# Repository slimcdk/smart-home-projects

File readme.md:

# Smart Home Projects
This collection of projects aim to minimize costs and vendor lock in associated with building a smart based home. Some projects are alternatives to existing products, often with added redundancy or improved features, such as local or manual control. This ensures control over devices when either electricity, network or third parties fail and renders your home more useless than traditional homes.

### What is supported?
Everything evolves around Home Assistant with the powerful ESPHome firmware powering each device. Both Home Assistant and ESPHome aims for a high quality codebase and guarantees high reliability and stability.
However, as all projects are based on Espressifs ESP chips, any compatible firmware, such as Tasmota or even custom Arduino code, can be used. This also opens the possibility to use the devices with other smart home projects or standalone.

### Base configurations
To maximize efficiency is every ESPHome configuration importing a set of common sensors and utilities through the [*packages*](https://esphome.io/guides/configuration-types.html#packages) integration. Base configurations can be found [here](https://github.com/slimcdk/home-server/blob/master/services/esphome/common).

---
## Projects

## [Thermostatic Radiator Valve](./trv)
Status: *Migrating model to FreeCAD*

Build costs is about €18.

## [Tablet Wall Mount](./tablet-wall-mount)
Status: *Cleaning up project repository*

## [Aurora Portable Light Pole](./aurora)
Status: *Cleaning up project repository*

## [Halo Clock Light](./halo-clock)
Status: *Cleaning up project repository*

## [Motorized Roller Shades](./roller-shades)
Status: *Working on hardware for position feedback*

## [LK Fuga Compatible Insert](./lkf-series)
Status: *Working on designing base*

## [Smart mirror (MagicMirror) ](./smart-mirror)
Status: *Working on model in FreeCAD*

## [Envriomental Sensor](./environmental-sensor)
Status: *Migrating model to FreeCAD*

## [Build on Ceiling Lights](./ceiling-spot)
Status: *On the drawing board*

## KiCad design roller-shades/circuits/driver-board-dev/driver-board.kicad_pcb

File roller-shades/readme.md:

# Motorized Roller Shades

---
### Parts list
#### Assembly parts list

#### Setup parts lists

---
### Assembly guide

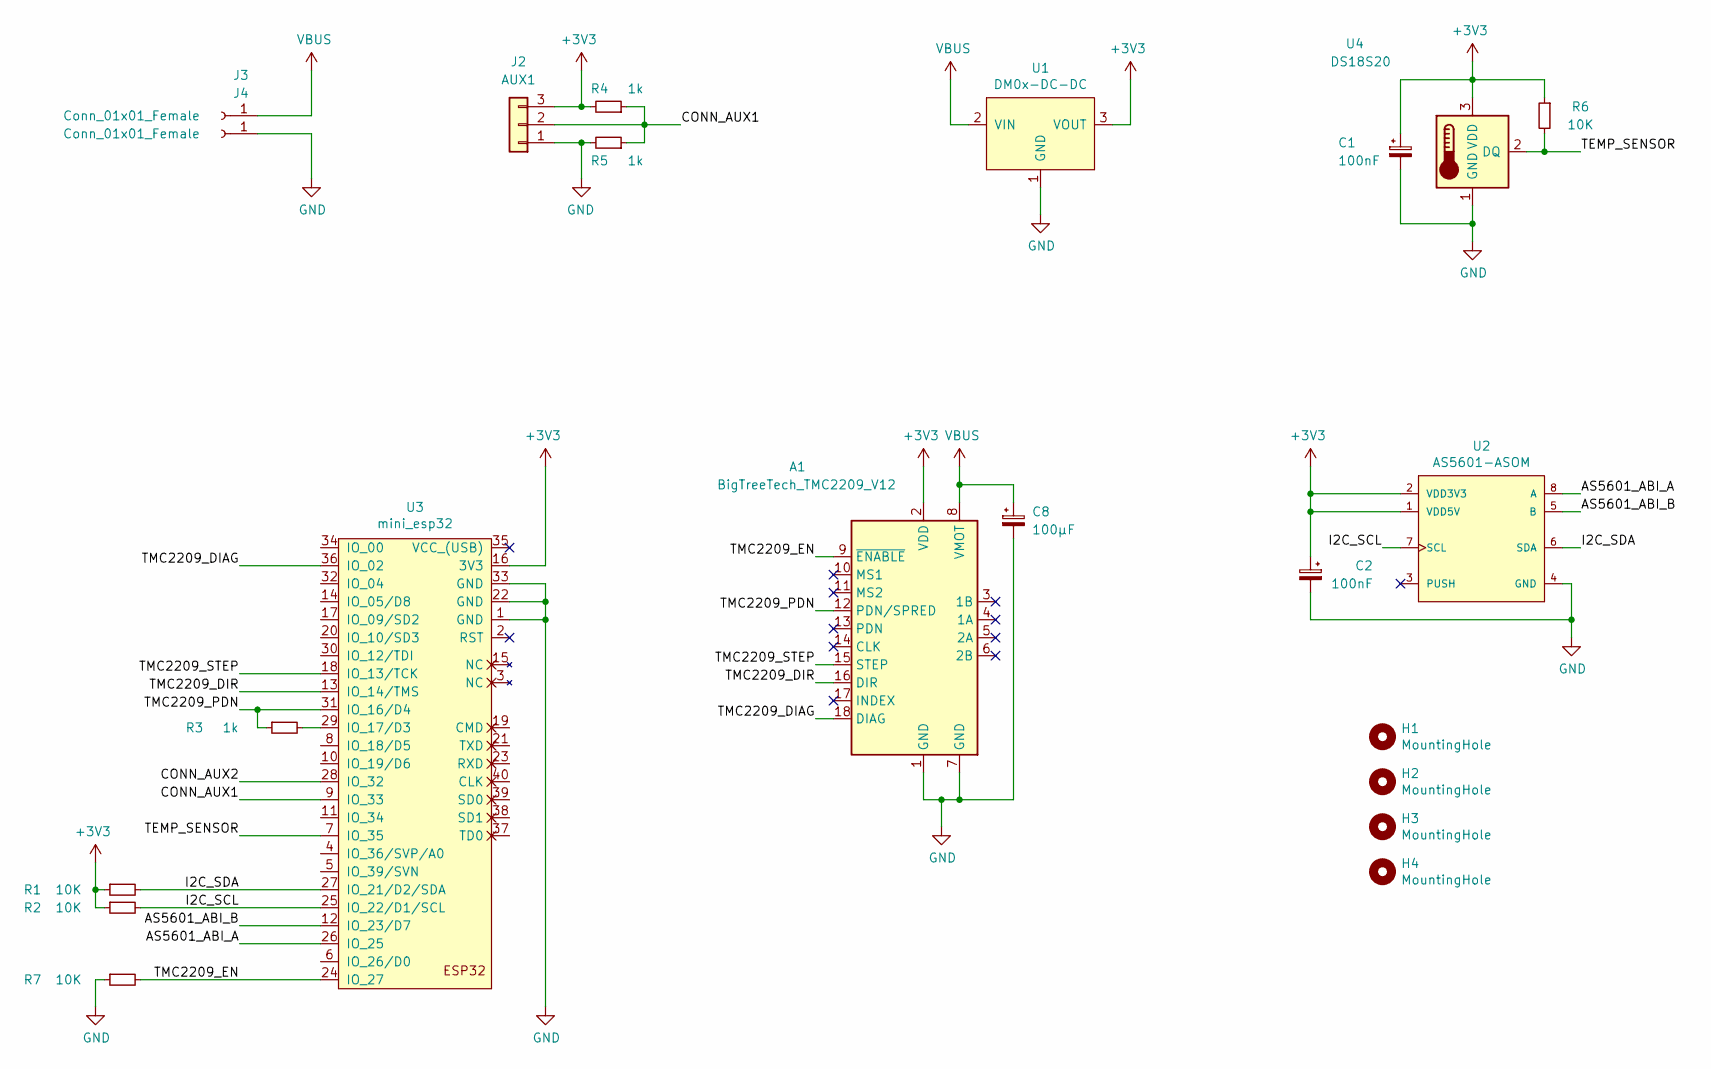
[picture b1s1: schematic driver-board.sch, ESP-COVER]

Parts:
A1: BigTreeTech_TMC2209_V12; BigTreeTech_TMC22xx_Breakout-16_15.2x20.3mm
C1, C2: 100nF; C_0805_2012Metric
C8: 100µF; CP_Radial_D5.0mm_P2.50mm
H1, H2, H3, H4: MountingHole; MountingHole_3.2mm_M3_DIN965_Pad
J2: AUX1; PinHeader_1x03_P2.54mm_Vertical
J3, J4: Conn_01x01_Female; TestPoint_THTPad_4.0x4.0mm_Drill2.0mm
R1, R2, R6, R7: 10K; R_0805_2012Metric_Pad1.20x1.40mm_HandSolder
R3, R4, R5: 1k; R_0805_2012Metric_Pad1.20x1.40mm_HandSolder
U1: DM0x-DC-DC; DM02-DC-DC
U2: AS5601-ASOM; Taos-AS5601-ASOM-0-0-0; mouser part number 985-AS5601-ASOM; digikey description ENCODER 12BIT PROGR A/B 8SOIC
U3: mini_esp32; Wemos_D1_mini32
U4: DS18S20; TO-92_Inline

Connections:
+3V3: A1.2 (VDD), C1.1, C2.1, J2.3, R1.1, R2.1, R4.2, R6.1, U1.3 (VOUT), U2.1 (VDD5V), U2.2 (VDD3V3), U3.16 (3V3), U4.3 (VDD)
/AS5601_ABI_A: U2.8 (A), U3.26 (IO_25)
/AS5601_ABI_B: U2.5 (B), U3.12 (IO_23/D7)
/CONN_AUX1: J2.2, R4.1, R5.1, U3.9 (IO_33)
/CONN_AUX2: U3.28 (IO_32)
/I2C_SCL: R2.2, U2.7 (SCL), U3.25 (IO_22/D1/SCL)
/I2C_SDA: R1.2, U2.6 (SDA), U3.27 (IO_21/D2/SDA)
/TEMP_SENSOR: R6.2, U3.7 (IO_35), U4.2 (DQ)
/TMC2209_DIAG: A1.18 (DIAG), U3.36 (IO_02)
/TMC2209_DIR: A1.16 (DIR), U3.13 (IO_14/TMS)
/TMC2209_EN: A1.9 (~ENABLE), R7.2, U3.24 (IO_27)
/TMC2209_PDN: A1.12 (PDN/SPRED), R3.1, U3.31 (IO_16/D4)
/TMC2209_STEP: A1.15 (STEP), U3.18 (IO_13/TCK)
GND: A1.1 (GND), A1.7 (GND), C1.2, C2.2, C8.2, J2.1, J4.1, R5.2, R7.1, U1.1 (GND), U2.4 (GND), U3.1 (GND), U3.22 (GND), U3.33 (GND), U4.1 (GND); also elsewhere on the board
unnamed: R3.2, U3.29 (IO_17/D3)
VBUS: A1.8 (VMOT), C8.1, J3.1, U1.2 (VIN); also elsewhere on the board

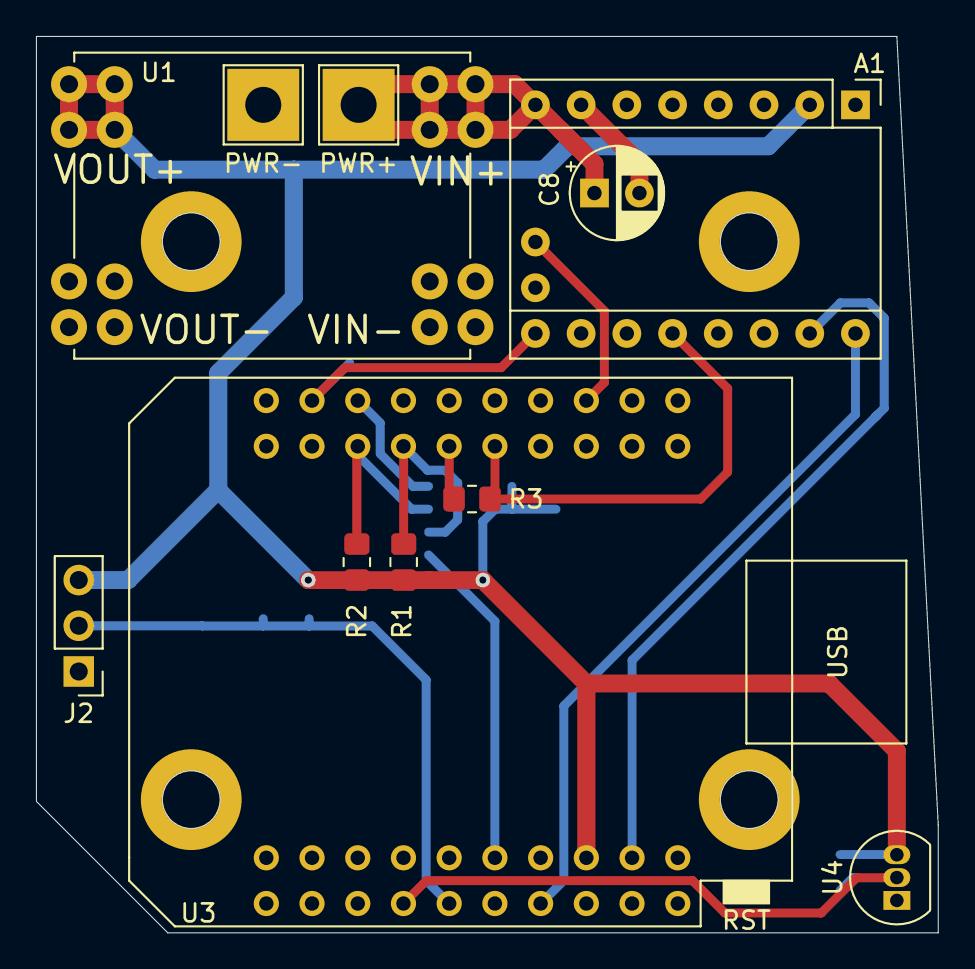
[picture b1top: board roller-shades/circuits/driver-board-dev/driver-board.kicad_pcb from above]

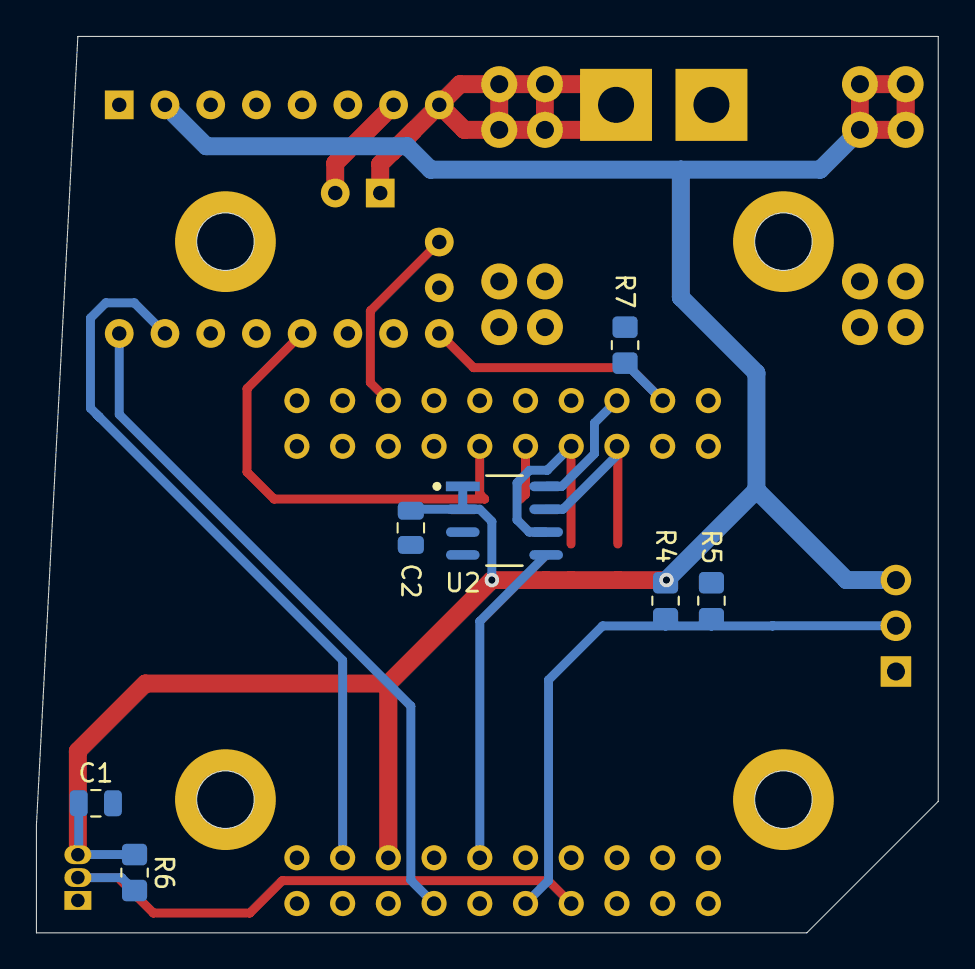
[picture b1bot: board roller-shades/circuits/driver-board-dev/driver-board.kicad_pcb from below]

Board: 2 copper layers, 50.1 x 49.8 mm, 22 parts (7 on the bottom side), 15 nets.

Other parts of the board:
PWR+: Conn_01x01_Female; TestPoint_THTPad_4.0x4.0mm_Drill2.0mm
PWR-: Conn_01x01_Female; TestPoint_THTPad_4.0x4.0mm_Drill2.0mm

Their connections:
GND: PWR-.1; also elsewhere on the board
VBUS: PWR+.1; also elsewhere on the board

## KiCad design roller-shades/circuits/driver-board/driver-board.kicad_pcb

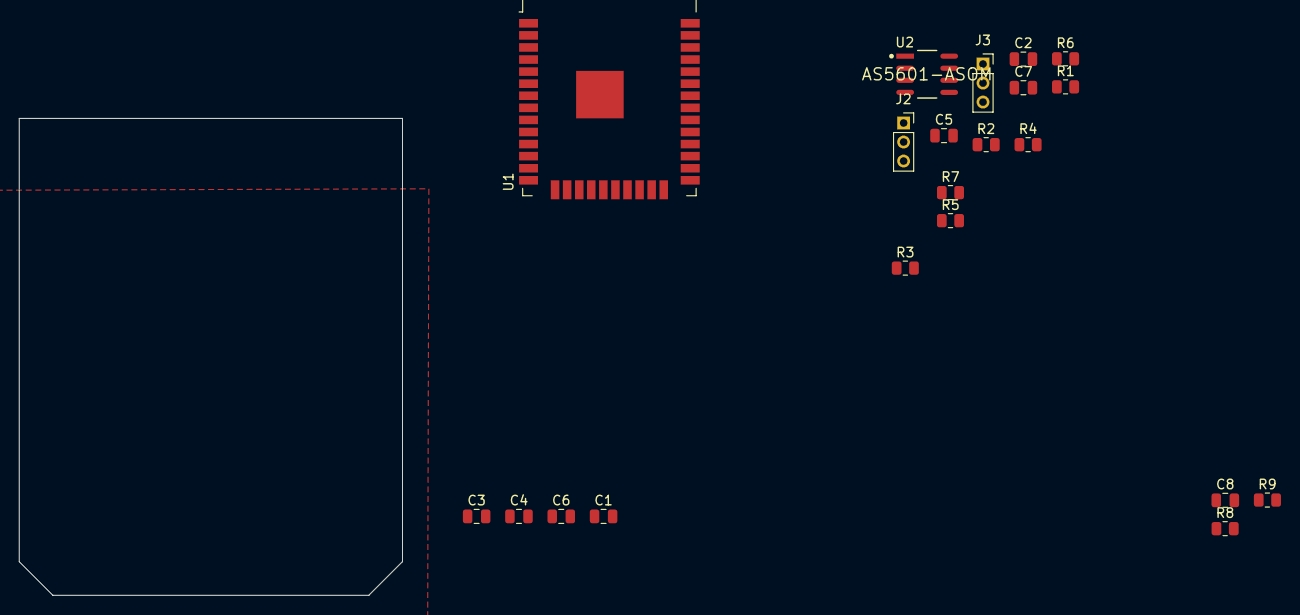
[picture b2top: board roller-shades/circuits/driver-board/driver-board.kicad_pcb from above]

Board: 2 copper layers, 40.3 x 50.1 mm, 21 parts (0 on the bottom side), 8 nets, no tracks yet.

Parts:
C1: 10µF 50V; C_0805_2012Metric
C2, C3, C7: 100nF; C_0805_2012Metric
C4: 220pF; C_0805_2012Metric
C5: NS; C_0805_2012Metric
C6: 22µF 6.3V; C_0805_2012Metric
C8: 100µF; C_0805_2012Metric
J2: AUX1; PinSocket_1x03_P2.00mm_Vertical
J3: AUX2; PinSocket_1x03_P2.00mm_Vertical
R1: 100K; R_0805_2012Metric
R2: 24.9K; R_0805_2012Metric
R3: 200K; R_0805_2012Metric
R4: 68.1K; R_0805_2012Metric
R5: 124K; R_0805_2012Metric
R6: 40.2K; R_0805_2012Metric
R7: 10K; R_0805_2012Metric
R8, R9: ??R; R_0805_2012Metric
U1: ESP32-WROOM-32
U2: AS5601-ASOM; Taos-AS5601-ASOM-0-0-0

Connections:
+3V3: C2.1, C6.1, C7.1, J2.3, J3.3, R5.2, R7.2, U2.1, U2.2
GND: C1.1, C2.2, C5.2, C6.2, C7.2, C8.2, J2.1, J3.1, R2.1, R3.2, R4.1, R6.1, R8.2, R9.2, U2.4
unnamed: C4.1, R4.2
unnamed: C4.2, C5.1
unnamed: R1.1, R2.2
unnamed: R5.1, R6.2
unnamed: U1.1, U1.15, U1.38, U1.39
VBUS: C1.2, C8.1, R1.2

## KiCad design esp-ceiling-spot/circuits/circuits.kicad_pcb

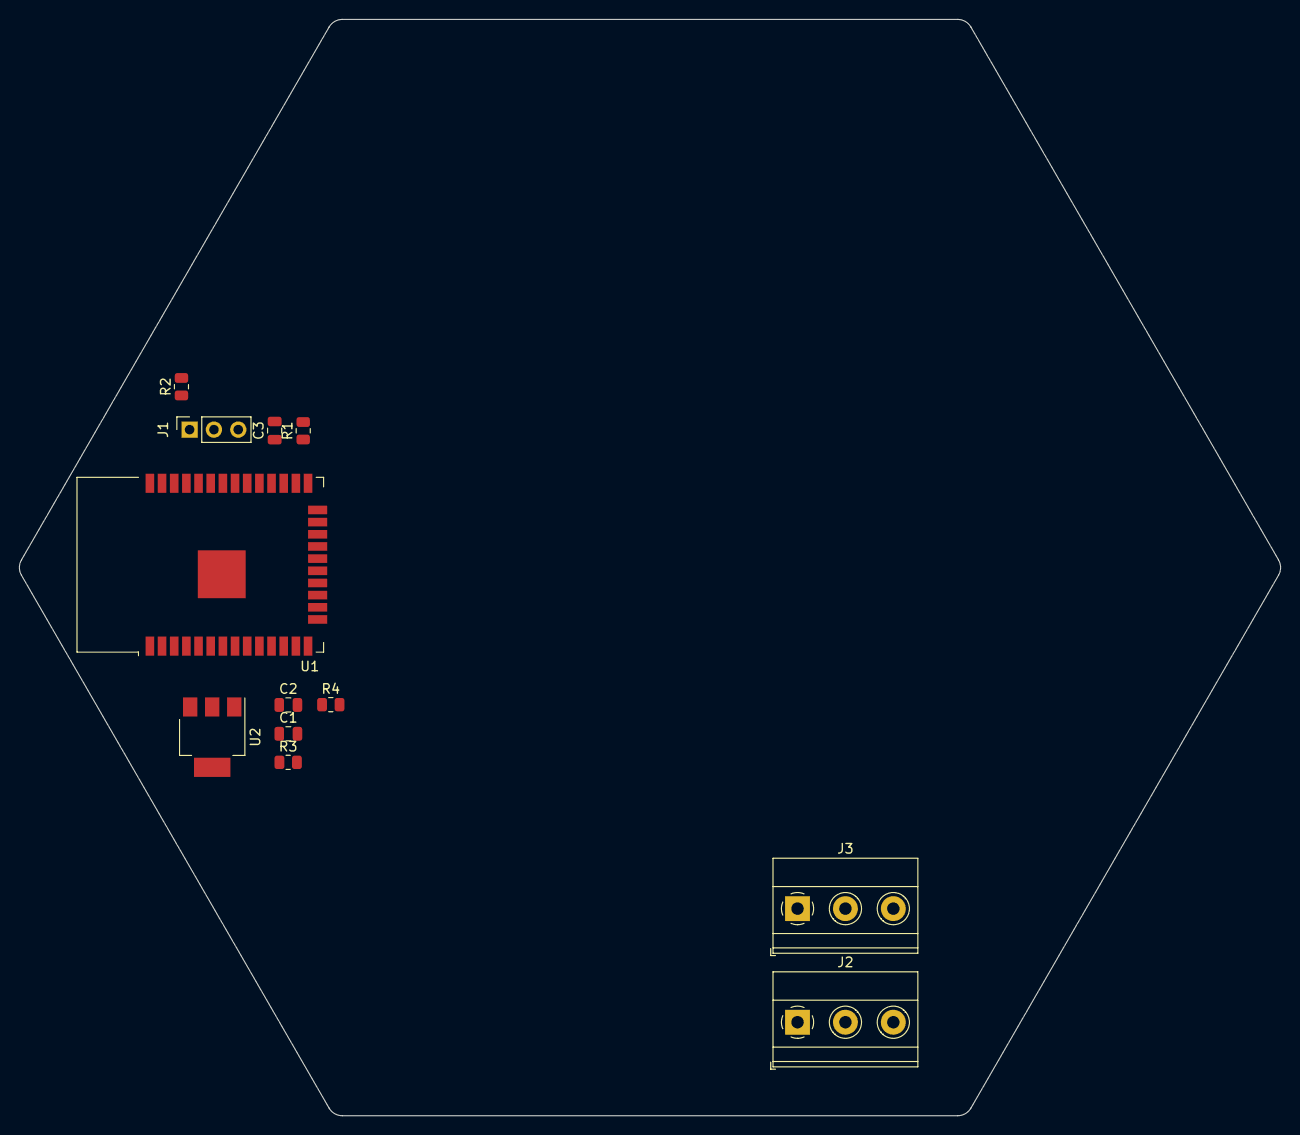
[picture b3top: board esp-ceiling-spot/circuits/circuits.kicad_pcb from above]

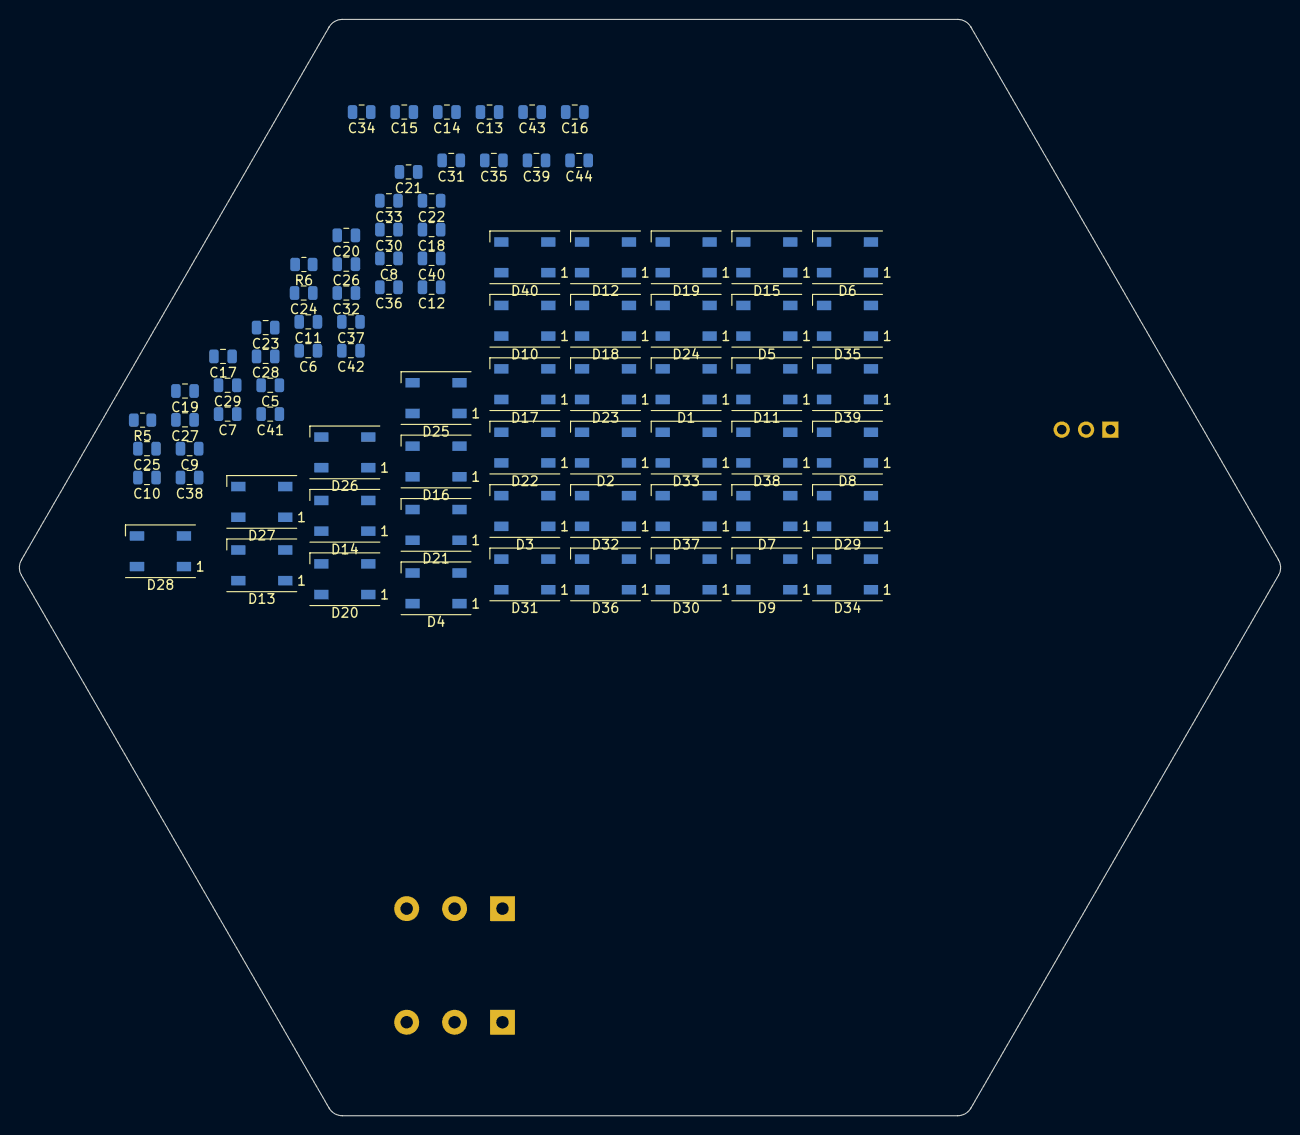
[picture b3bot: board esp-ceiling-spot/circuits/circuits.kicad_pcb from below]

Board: 2 copper layers, 131.7 x 114.4 mm, 94 parts (82 on the bottom side), 53 nets, no tracks yet.

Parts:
C1: 10µF; C_0805_2012Metric
C2: 22µF; C_0805_2012Metric
C3: ESP 10µF 0805; C_0805_2012Metric
C5, C6, C7, C8, C9, C10, C11, C12, C13, C14, C15, C16, C17, C18, C19, C20, C21, C22, C23, C24, C25, C26, C27, C28, C29, C30, C31, C32, C33, C34, C35, C36, C37, C38, C39, C40, C41, C42, C43, C44: 100nF; C_0805_2012Metric
D1, D2, D3, D4, D5, D6, D7, D8, D9, D10, D11, D12, D13, D14, D15, D16, D17, D18, D19, D20, D21, D22, D23, D24, D25, D26, D27, D28, D29, D30, D31, D32, D33, D34, D35, D36, D37, D38, D39, D40: WS2812B; LED_WS2812B_PLCC4_5.0x5.0mm_P3.2mm
J1: RGB LED RING; PinSocket_1x03_P2.54mm_Vertical
J2, J3: External 230AC; TerminalBlock_Phoenix_MKDS-1,5-3_1x03_P5.00mm_Horizontal
R1, R2, R3, R4: 10K 0805; R_0805_2012Metric
R5, R6: 500R; R_0805_2012Metric
U1: ESP32-WROOM-32D; ESP32-WROOM-32
U2: AMS1117-3.3; SOT-223-3_TabPin2

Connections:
+3V3: C2.1, C3.1, R1.1, R2.1, R3.1, U1.2, U2.2
+5V: C1.1, C5.1, C6.1, C7.1, C8.1, C9.1, C10.1, C11.1, C12.1, C13.1, C14.1, C15.1, C16.1, C17.1, C18.1, C19.1, C20.1, C21.1, C22.1, C23.1, C24.1, C25.1, C26.1, C27.1, C28.1, C29.1, C30.1, C31.1, C32.1, C33.1, C34.1, C35.1, C36.1, C37.1, C38.1, C39.1, C40.1, C41.1, C42.1, C43.1, C44.1, D1.1, D2.1, D3.1, D4.1, D5.1, D6.1, D7.1, D8.1, D9.1, D10.1, D11.1, D12.1, D13.1, D14.1, D15.1, D16.1, D17.1, D18.1, D19.1, D20.1, D21.1, D22.1, D23.1, D24.1, D25.1, D26.1, D27.1, D28.1, D29.1, D30.1, D31.1, D32.1, D33.1, D34.1, D35.1, D36.1, D37.1, D38.1, D39.1, D40.1, J1.1, U2.3
/EARTH: J2.3, J3.3
/ESP_EN: R1.2, U1.3
/ESP_IO5: R2.2, U1.29
/ESP_IO12: R4.2, U1.14
/ESP_IO15: R3.2, U1.23
/LIVE: J2.2, J3.2
/NEUTRAL: J2.1, J3.1
/RGB_RING_SIG: J1.2, U1.27
/RGB_SIG: R5.2, U1.28
GND: C1.2, C2.2, C3.2, C5.2, C6.2, C7.2, C8.2, C9.2, C10.2, C11.2, C12.2, C13.2, C14.2, C15.2, C16.2, C17.2, C18.2, C19.2, C20.2, C21.2, C22.2, C23.2, C24.2, C25.2, C26.2, C27.2, C28.2, C29.2, C30.2, C31.2, C32.2, C33.2, C34.2, C35.2, C36.2, C37.2, C38.2, C39.2, C40.2, C41.2, C42.2, C43.2, C44.2, D1.3, D2.3, D3.3, D4.3, D5.3, D6.3, D7.3, D8.3, D9.3, D10.3, D11.3, D12.3, D13.3, D14.3, D15.3, D16.3, D17.3, D18.3, D19.3, D20.3, D21.3, D22.3, D23.3, D24.3, D25.3, D26.3, D27.3, D28.3, D29.3, D30.3, D31.3, D32.3, D33.3, D34.3, D35.3, D36.3, D37.3, D38.3, D39.3, D40.3, J1.3, R4.1, R6.1, U1.1, U1.15, U1.38, U1.39, U2.1
unnamed: D1.2, D5.4
unnamed: D1.4, R5.1
unnamed: D2.2, D6.4
unnamed: D2.4, D37.2
unnamed: D3.2, D7.4
unnamed: D3.4, D38.2
unnamed: D4.2, D8.4
unnamed: D5.2, D9.4
unnamed: D10.2, D14.4
unnamed: D6.2, D10.4
unnamed: D11.2, D15.4
unnamed: D7.2, D11.4
unnamed: D12.2, D16.4
unnamed: D8.2, D12.4
unnamed: D13.2, D17.4
unnamed: D9.2, D13.4
unnamed: D14.2, D18.4
unnamed: D15.2, D19.4
unnamed: D16.2, D20.4
unnamed: D17.2, D21.4
unnamed: D18.2, D22.4
unnamed: D19.2, D23.4
unnamed: D20.2, D24.4
unnamed: D21.2, D25.4
unnamed: D22.2, D26.4
unnamed: D23.2, D27.4
unnamed: D24.2, D28.4
unnamed: D25.2, D29.4
unnamed: D26.2, D30.4
unnamed: D27.2, D31.4
unnamed: D28.2, D32.4
unnamed: D29.2, D33.4
unnamed: D30.2, D34.4
unnamed: D31.2, D35.4
unnamed: D32.2, D36.4
unnamed: D33.2, D37.4
unnamed: D34.2, D38.4
unnamed: D35.2, D39.4
unnamed: D36.2, D40.4
unnamed: D4.4, D39.2
unnamed: D40.2, R6.2

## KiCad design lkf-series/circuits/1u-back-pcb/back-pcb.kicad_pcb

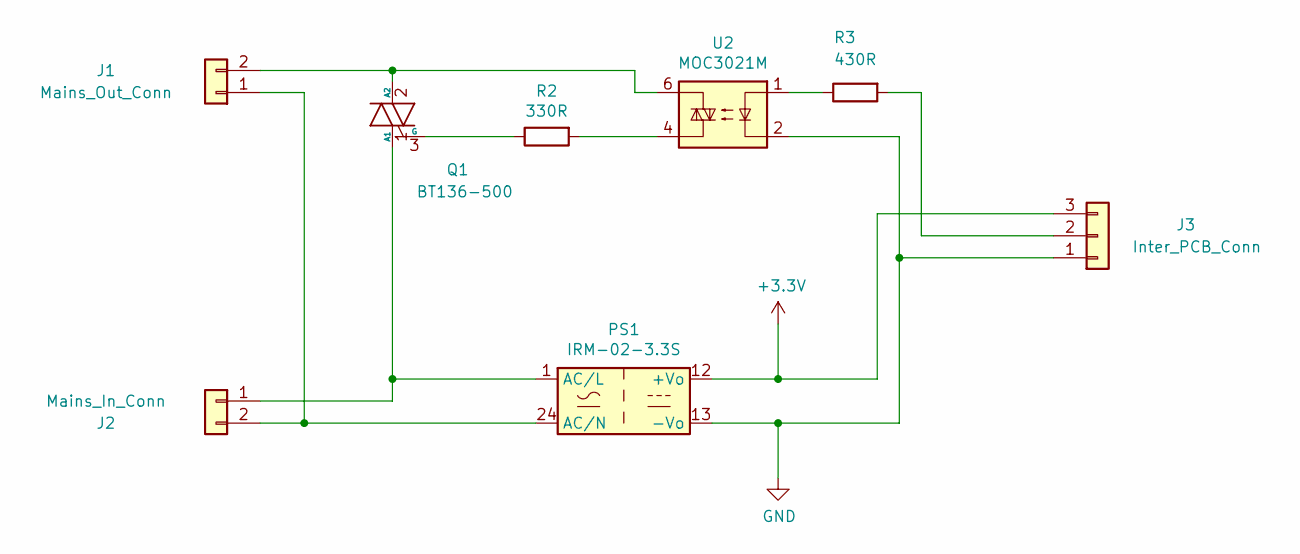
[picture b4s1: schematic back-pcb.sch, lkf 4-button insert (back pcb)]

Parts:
J1: Mains_Out_Conn; 2061-602_998-404
J2: Mains_In_Conn; 2061-602_998-404
J3: Inter_PCB_Conn; PinHeader_1x03_P2.54mm_Vertical
PS1: IRM-02-3.3S; Converter_ACDC_MeanWell_IRM-02-xx_SMD
Q1: BT136-500; TO-252-2
R2: 330R; R_1210_3225Metric
R3: 430R; R_0603_1608Metric
U2: MOC3021M; DIP-6_W7.62mm_SMDSocket_SmallPads

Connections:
+3V3: J3.3, PS1.12 (+Vo)
GND: J3.1, PS1.13 (-Vo), U2.2
unnamed: J1.1, J2.2, PS1.24 (AC/N)
unnamed: J1.2, Q1.2 (A2), U2.6
unnamed: J2.1, PS1.1 (AC/L), Q1.1 (A1)
unnamed: J3.2, R3.2
unnamed: Q1.3 (G), R2.1
unnamed: R2.2, U2.4
unnamed: R3.1, U2.1

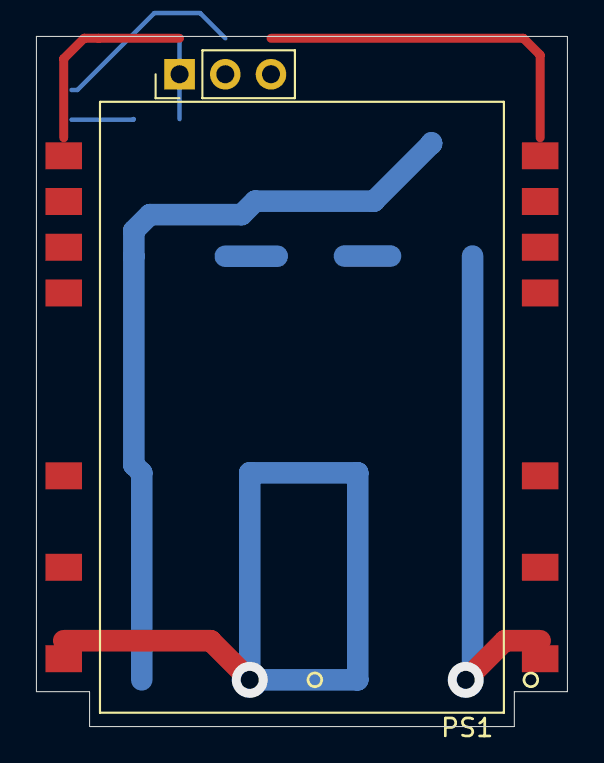
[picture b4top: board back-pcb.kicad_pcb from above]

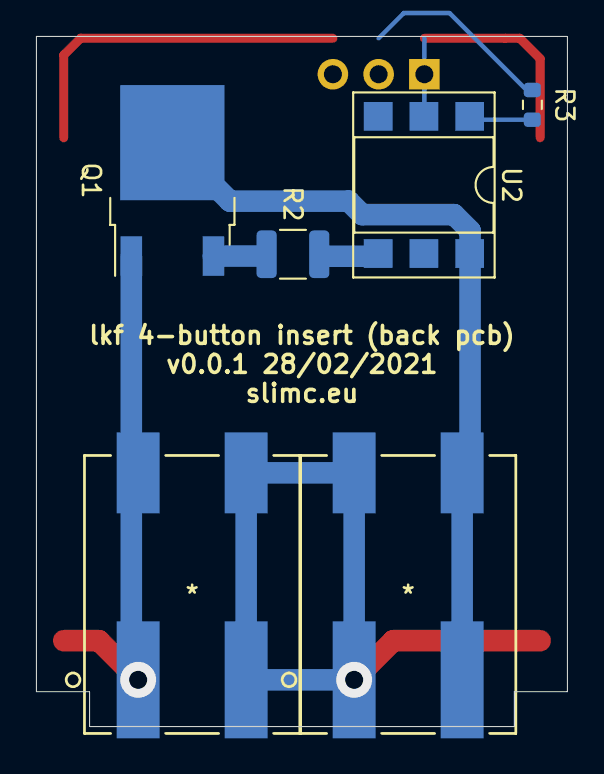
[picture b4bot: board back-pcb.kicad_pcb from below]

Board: 2 copper layers, 29.5 x 38.3 mm, 8 parts (6 on the bottom side), 9 nets.

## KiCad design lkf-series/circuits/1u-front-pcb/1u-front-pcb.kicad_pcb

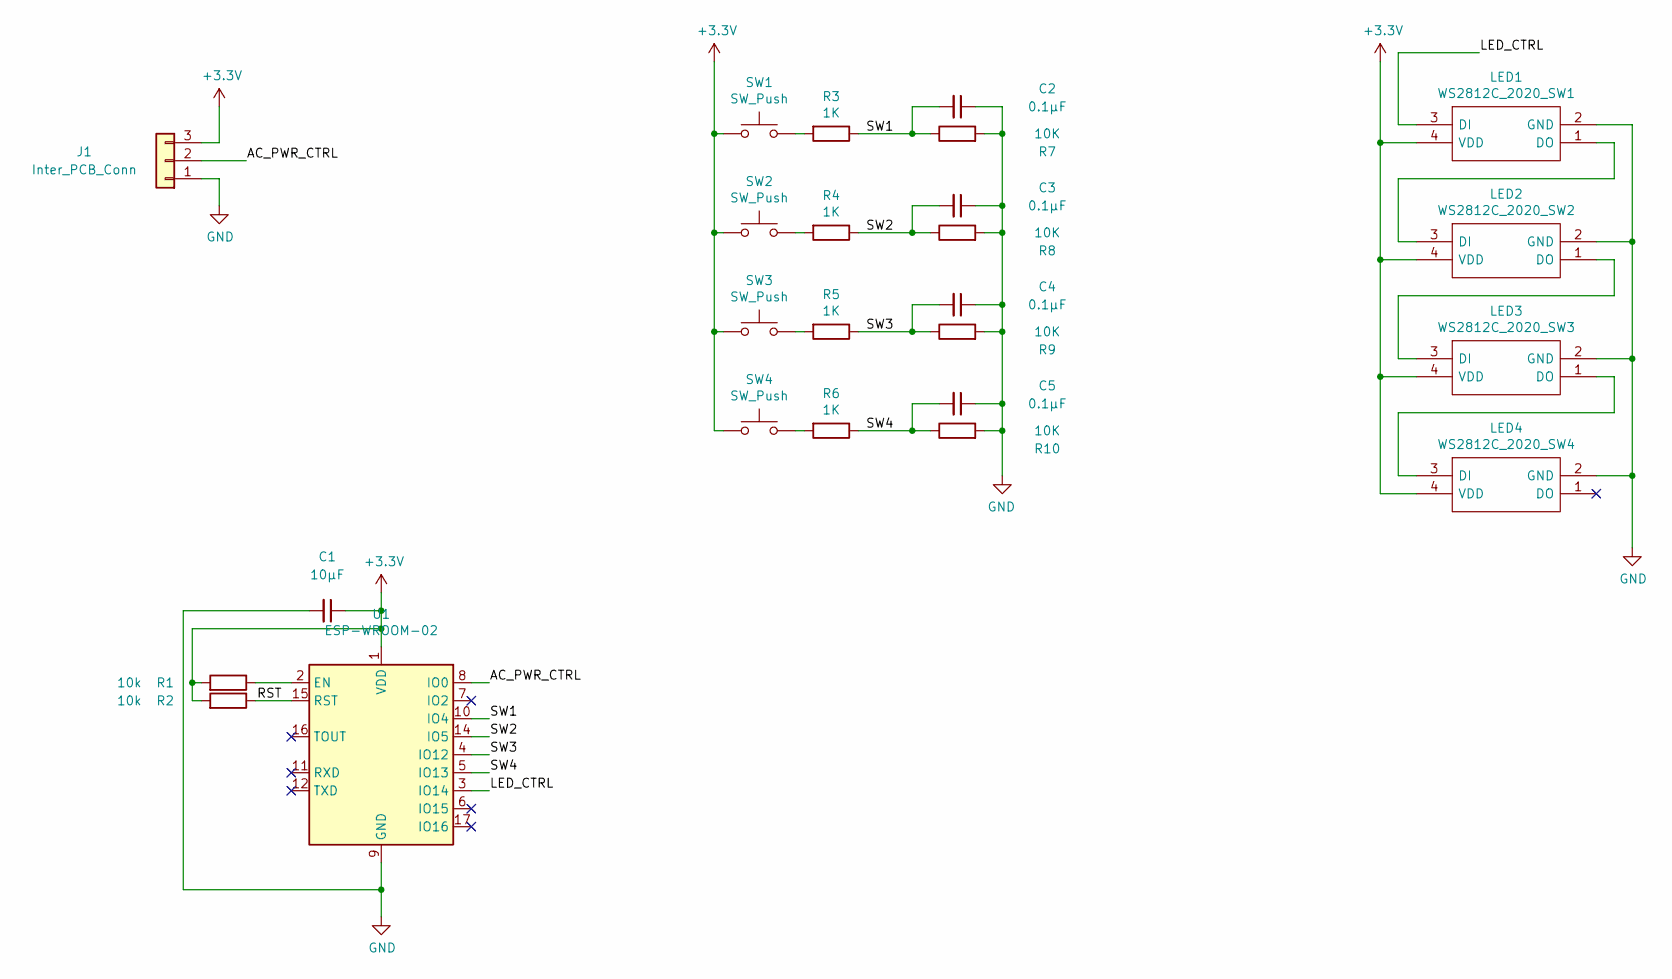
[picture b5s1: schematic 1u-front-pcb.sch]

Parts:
C1: 10µF; C_0603_1608Metric
C2, C3, C4, C5: 0.1µF; C_0603_1608Metric
J1: Inter_PCB_Conn; PinHeader_1x03_P2.54mm_Vertical
LED1: WS2812C_2020_SW1; WS2812C2020; Manufacturer_Part_Number WS2812C-2020
LED2: WS2812C_2020_SW2; WS2812C2020; Manufacturer_Part_Number WS2812C-2020
LED3: WS2812C_2020_SW3; WS2812C2020; Manufacturer_Part_Number WS2812C-2020
LED4: WS2812C_2020_SW4; WS2812C2020; Manufacturer_Part_Number WS2812C-2020
R1, R2: 10k; R_0603_1608Metric
R3, R4, R5, R6: 1K; R_0603_1608Metric
R7, R8, R9, R10: 10K; R_0603_1608Metric
SW1, SW2, SW3, SW4: SW_Push; SW_SPST_TL3342
U1: ESP-WROOM-02

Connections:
+3V3: C1.1, J1.3, LED1.4 (VDD), LED2.4 (VDD), LED3.4 (VDD), LED4.4 (VDD), R1.2, R2.2, SW1.1, SW2.1, SW3.1, SW4.1, U1.1 (VDD)
/AC_PWR_CTRL: J1.2, U1.8 (IO0)
/LED_CTRL: LED1.3 (DI), U1.3 (IO14)
/RST: R2.1, U1.15 (RST)
/SW1: C2.2, R3.1, R7.1, U1.10 (IO4)
/SW2: C3.2, R4.1, R8.1, U1.14 (IO5)
/SW3: C4.2, R5.1, R9.1, U1.4 (IO12)
/SW4: C5.2, R6.1, R10.1, U1.5 (IO13)
GND: C1.2, C2.1, C3.1, C4.1, C5.1, J1.1, LED1.2 (GND), LED2.2 (GND), LED3.2 (GND), LED4.2 (GND), R7.2, R8.2, R9.2, R10.2, U1.9 (GND), U1.13 (GND), U1.18 (GND)
unnamed: LED1.1 (DO), LED2.3 (DI)
unnamed: LED2.1 (DO), LED3.3 (DI)
unnamed: LED3.1 (DO), LED4.3 (DI)
unnamed: R1.1, U1.2 (EN)
unnamed: R3.2, SW1.2
unnamed: R4.2, SW2.2
unnamed: R5.2, SW3.2
unnamed: R6.2, SW4.2

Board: 2 copper layers, 25 parts (1 on the bottom side), 17 nets, no tracks yet.

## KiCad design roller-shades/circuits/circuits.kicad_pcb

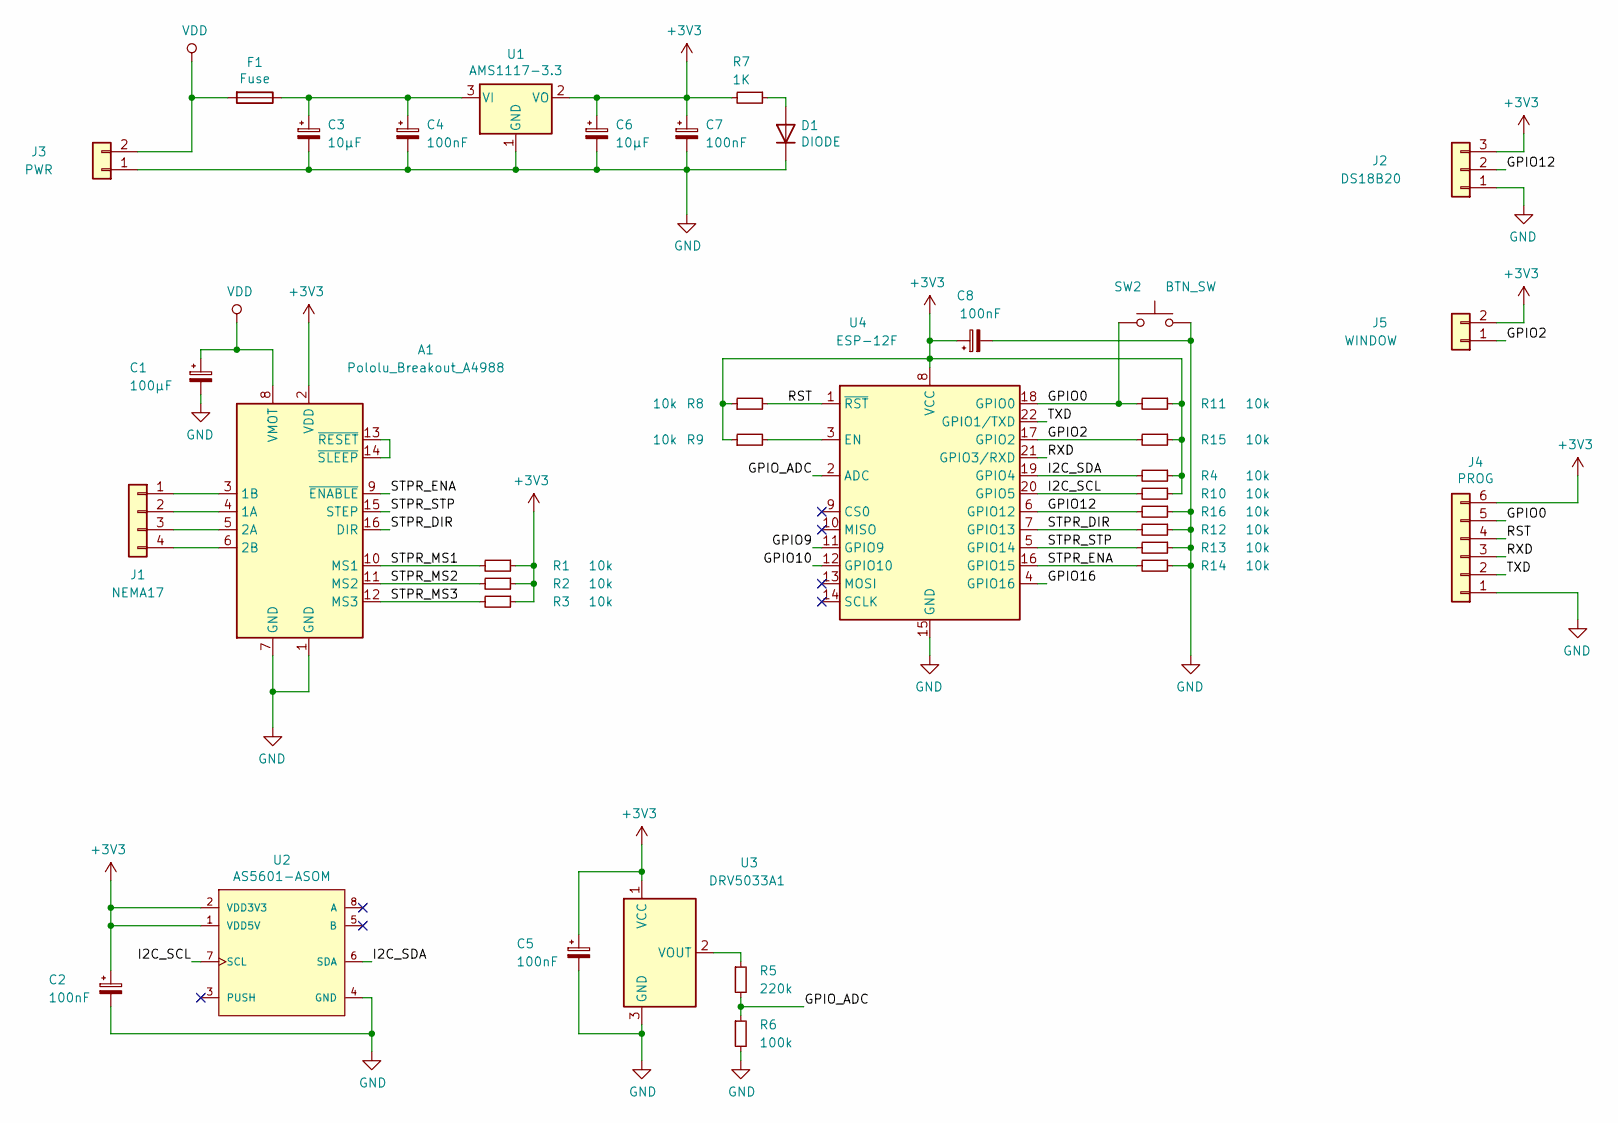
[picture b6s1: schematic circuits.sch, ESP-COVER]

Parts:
A1: Pololu_Breakout_A4988; Pololu_Breakout-16_15.2x20.3mm
C1: 100µF; CP_Elec_6.3x7.7
C2, C4, C5, C7: 100nF; C_0603_1608Metric
C3, C6: 10µF; C_0603_1608Metric
C8: 100nF; Fuse_0805_2012Metric
D1: DIODE; D_0805_2012Metric
F1: Fuse; Fuse_0603_1608Metric
J1: NEMA17; PinHeader_1x04_P2.54mm_Vertical
J2: DS18B20; PinSocket_1x03_P2.00mm_Vertical
J3: PWR; PinHeader_1x02_P2.54mm_Vertical
J4: PROG; PinHeader_1x06_P2.00mm_Vertical
J5: WINDOW; PinHeader_1x02_P2.54mm_Vertical
R1, R2, R3, R4, R8, R9, R10, R11, R12, R13, R14, R15, R16: 10k; R_0603_1608Metric; LCSC C365360
R5: 220k; R_0603_1608Metric; LCSC C365360
R6: 100k; R_0603_1608Metric; LCSC C365360
R7: 1K; R_0603_1608Metric; LCSC C365360
SW2: BTN_SW; SW_DIP_SPSTx01_Slide_Copal_CHS-01A_W5.08mm_P1.27mm_JPin
U1: AMS1117-3.3; SOT-223-3_TabPin2
U2: AS5601-ASOM; Taos-AS5601-ASOM-0-0-0; mouser part number 985-AS5601-ASOM; digikey description ENCODER 12BIT PROGR A/B 8SOIC
U3: DRV5033A1; TO-92Flat
U4: ESP-12F; ESP-12E

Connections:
+3V3: A1.2 (VDD), C2.1, C5.1, C6.1, C7.1, C8.1, J2.3, J4.6, J5.2, R1.1, R2.1, R3.1, R4.1, R7.2, R8.1, R9.1, R10.1, R11.1, R15.1, U1.2 (VO), U2.1 (VDD5V), U2.2 (VDD3V3), U3.1 (VCC), U4.8 (VCC)
/GPIO0: J4.5, R11.2, SW2.1, U4.18 (GPIO0)
/GPIO2: J5.1, R15.2, U4.17 (GPIO2)
/GPIO9: U4.11 (GPIO9)
/GPIO10: U4.12 (GPIO10)
/GPIO12: J2.2, R16.2, U4.6 (GPIO12)
/GPIO16: U4.4 (GPIO16)
/GPIO_ADC: R5.2, R6.1, U4.2 (ADC)
/I2C_SCL: R10.2, U2.7 (SCL), U4.20 (GPIO5)
/I2C_SDA: R4.2, U2.6 (SDA), U4.19 (GPIO4)
/RST: J4.4, R8.2, U4.1 (~RST)
/RXD: J4.3, U4.21 (GPIO3/RXD)
/STPR_DIR: A1.16 (DIR), R12.2, U4.7 (GPIO13)
/STPR_ENA: A1.9 (~ENABLE), R14.2, U4.16 (GPIO15)
/STPR_MS1: A1.10 (MS1), R1.2
/STPR_MS2: A1.11 (MS2), R2.2
/STPR_MS3: A1.12 (MS3), R3.2
/STPR_STP: A1.15 (STEP), R13.2, U4.5 (GPIO14)
/TXD: J4.2, U4.22 (GPIO1/TXD)
GND: A1.1 (GND), A1.7 (GND), C1.2, C2.2, C3.2, C4.2, C5.2, C6.2, C7.2, C8.2, D1.2 (K), J2.1, J3.1, J4.1, R6.2, R12.1, R13.1, R14.1, R16.1, SW2.2, U1.1 (GND), U2.4 (GND), U3.3 (GND), U4.15 (GND)
unnamed: A1.3 (1B), J1.1
unnamed: A1.4 (1A), J1.2
unnamed: A1.5 (2A), J1.3
unnamed: A1.6 (2B), J1.4
unnamed: A1.13 (~RESET), A1.14 (~SLEEP)
unnamed: C3.1, C4.1, F1.1, U1.3 (VI)
unnamed: D1.1 (A), R7.1
unnamed: R5.1, U3.2 (VOUT)
unnamed: R9.2, U4.3 (EN)
VDD: A1.8 (VMOT), C1.1, F1.2, J3.2

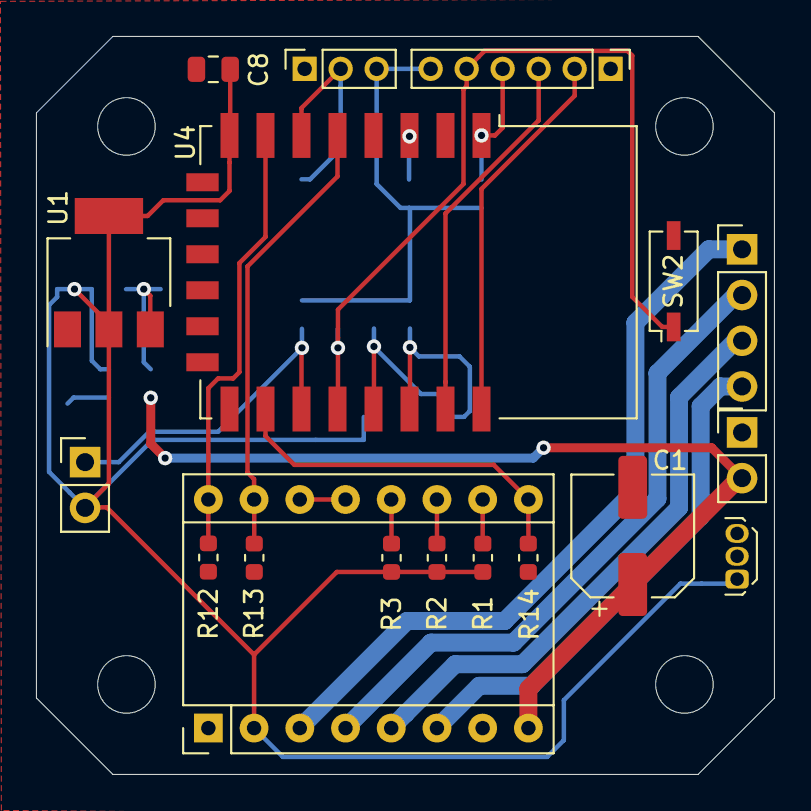
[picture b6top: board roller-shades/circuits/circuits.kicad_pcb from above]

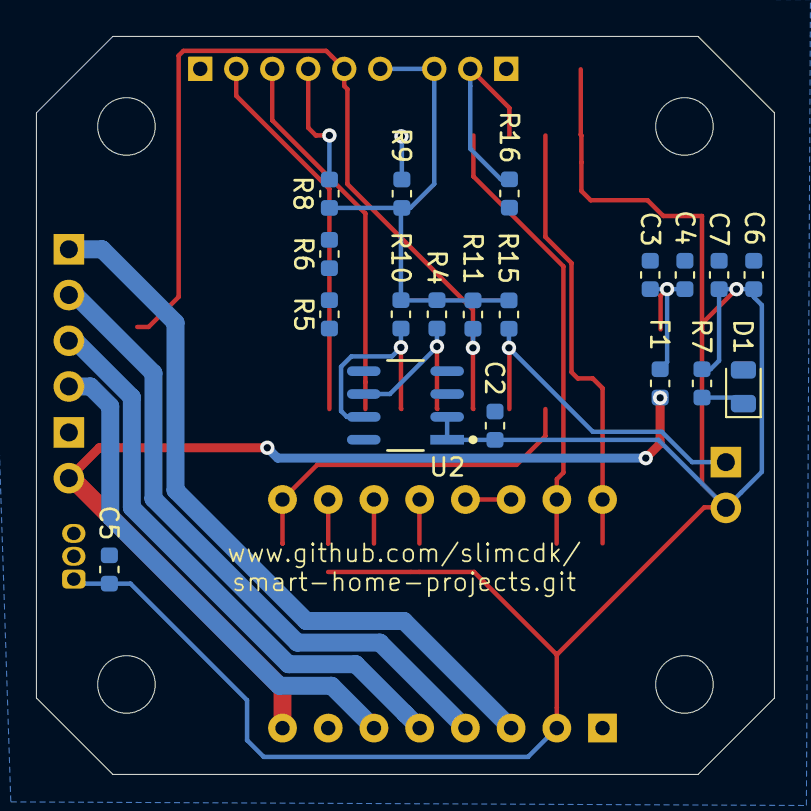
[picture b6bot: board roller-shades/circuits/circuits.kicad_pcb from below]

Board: 2 copper layers, 41.0 x 41.0 mm, 37 parts (19 on the bottom side), 27 nets.

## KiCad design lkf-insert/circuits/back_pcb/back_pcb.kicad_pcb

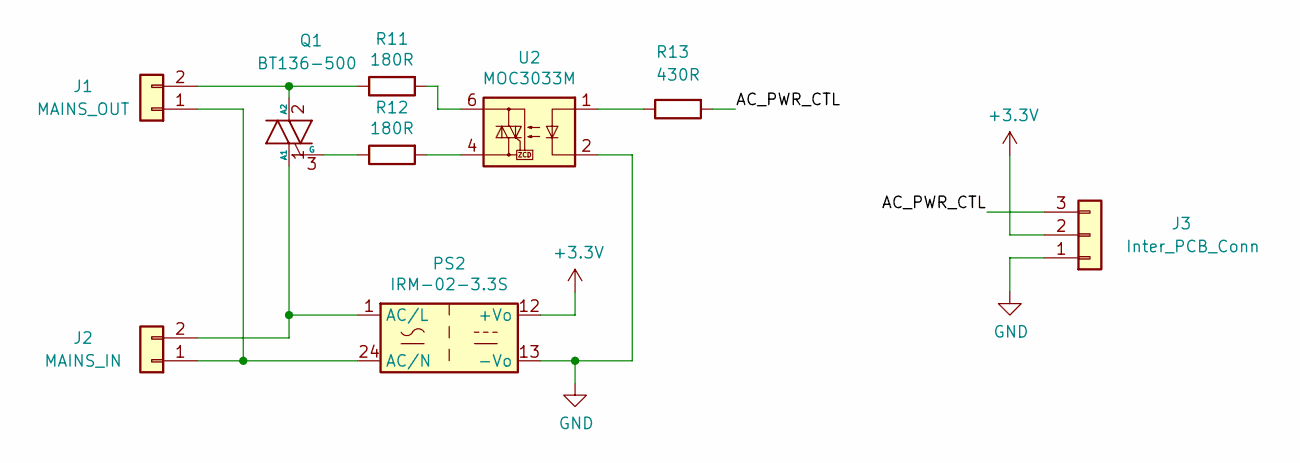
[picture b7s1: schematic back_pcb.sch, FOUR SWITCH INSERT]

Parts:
J1: MAINS_OUT; 2061-602_998-404
J2: MAINS_IN; 2061-602_998-404
J3: Inter_PCB_Conn; PinHeader_1x03_P2.54mm_Vertical
PS2: IRM-02-3.3S; Converter_ACDC_MeanWell_IRM-02-xx_SMD
Q1: BT136-500; TO-252-2
R11, R12: 180R; R_0603_1608Metric
R13: 430R; R_0603_1608Metric
U2: MOC3033M; DIP-6_W7.62mm_SMDSocket_SmallPads

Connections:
+3V3: J3.2, PS2.12 (+Vo)
/AC_PWR_CTL: J3.3, R13.2
GND: J3.1, PS2.13 (-Vo), U2.2
unnamed: J1.1, J2.1, PS2.24 (AC/N)
unnamed: J1.2, Q1.2 (A2), R11.1
unnamed: J2.2, PS2.1 (AC/L), Q1.1 (A1)
unnamed: Q1.3 (G), R12.1
unnamed: R11.2, U2.6
unnamed: R12.2, U2.4
unnamed: R13.1, U2.1

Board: 2 copper layers, 9 parts (7 on the bottom side), 10 nets, no tracks yet.

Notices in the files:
parts and their libraries:
Copyright 2016 Accelerated Designs. All rights reserved.
